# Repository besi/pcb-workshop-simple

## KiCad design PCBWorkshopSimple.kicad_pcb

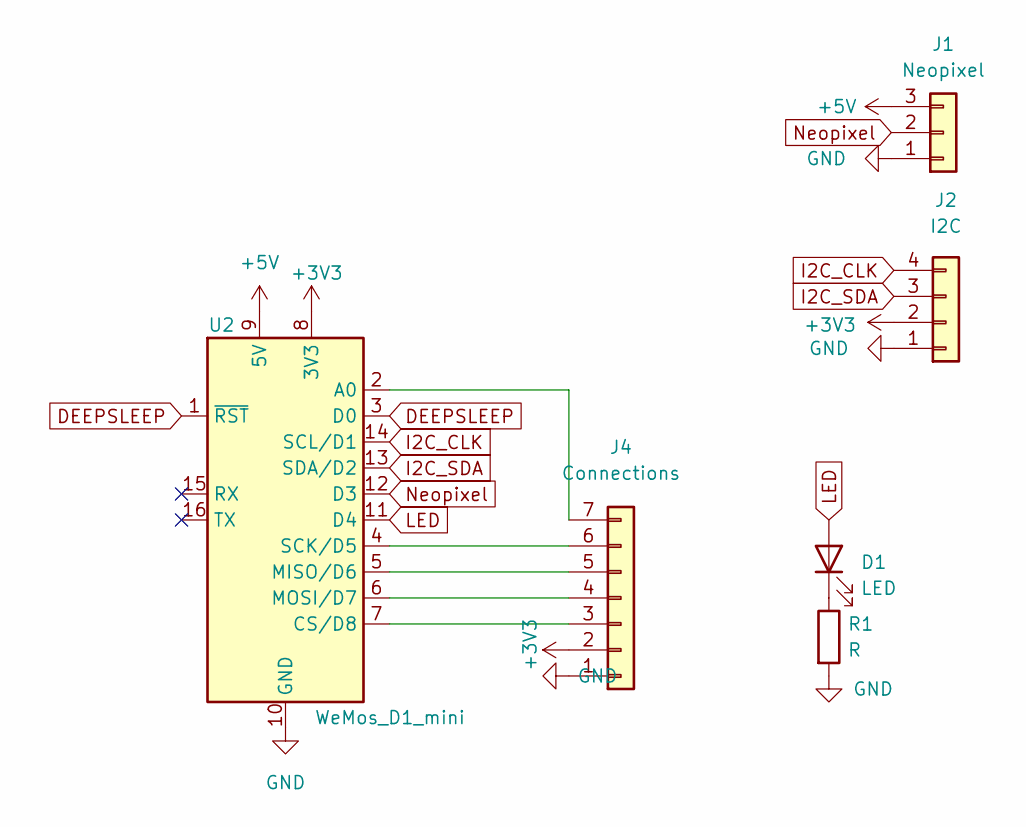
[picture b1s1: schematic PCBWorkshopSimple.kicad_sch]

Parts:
D1: LED; LED_D5.0mm
J1: Neopixel; PinHeader_1x03_P2.54mm_Vertical
J2: I2C; PinHeader_1x04_P2.00mm_Vertical
J4: Connections; PinHeader_1x07_P2.54mm_Vertical
R1: R; R_Axial_DIN0207_L6.3mm_D2.5mm_P7.62mm_Horizontal
U2: WeMos_D1_mini; WEMOS_D1_mini_light

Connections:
+3V3: J2.2, J4.2, U2.8 (3V3)
+5V: J1.3, U2.9 (5V)
/ANDRIS_SPEZIAL: J4.4, U2.6 (MOSI/D7)
DEEPSLEEP: U2.1 (~RST), U2.3 (D0)
GND: J1.1, J2.1, J4.1, R1.2, U2.10 (GND)
I2C_CLK: J2.4, U2.14 (SCL/D1)
I2C_SDA: J2.3, U2.13 (SDA/D2)
LED: D1.2 (A), U2.11 (D4)
Neopixel: J1.2, U2.12 (D3)
unnamed: D1.1 (K), R1.1
unnamed: J4.3, U2.7 (CS/D8)
unnamed: J4.5, U2.5 (MISO/D6)
unnamed: J4.6, U2.4 (SCK/D5)
unnamed: J4.7, U2.2 (A0)

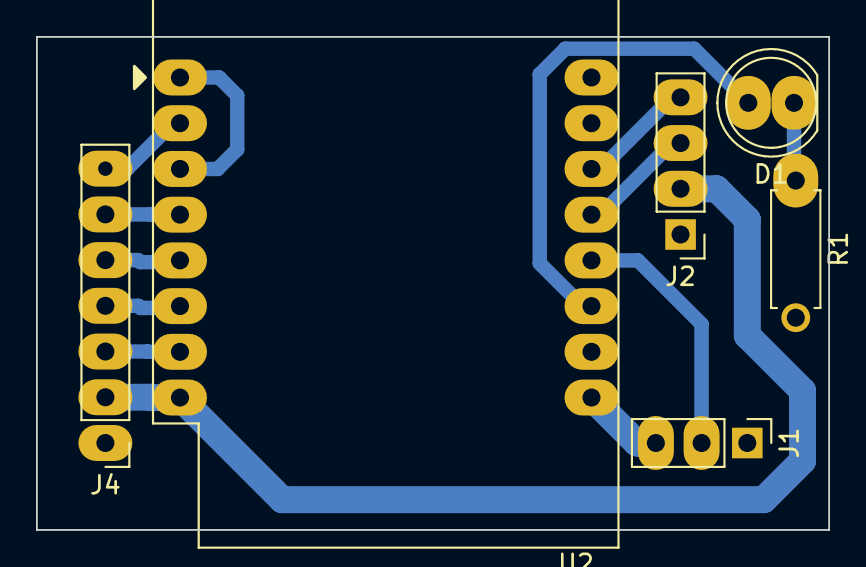
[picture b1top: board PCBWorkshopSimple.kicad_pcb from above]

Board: 2 copper layers, 44.0 x 27.4 mm, 6 parts (0 on the bottom side), 14 nets.

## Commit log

2023-02-25 Final touches
2023-02-25 Upload plot files
